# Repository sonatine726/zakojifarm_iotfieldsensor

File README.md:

# 座光寺農園の田んぼの環境センシングIoT機器

# 機能仕様

1. 設置した田んぼの気温、気圧、水位、GPS座標、バッテリー残量といったデータを定期的に計測する
2. 1で計測したデータをLTEでWEBサーバにアップロードする
3. 間欠動作でバッテリー交換無しで１シーズンの長期間駆動を実現する
4. 2のデータはWEBブラウザやスマートフォンアプリで、時系列順の参照や統計処理を可能にする
5. 4のデータに対してメールやMQTTによるアラート通知を可能にする
6. 自動水門開閉機能といった将来的な機能拡張が可能な機構や設計にする

# 成果物の形式と保管場所
## ハードウェア
### 機構
CADデータは Fusion360で作成。保管はFusion Team のクラウドストレージを使用する。
それ以外のデータは本リポジトリに保管。

### 基板
基板データはKiCadで作成。保管は本リポジトリ。

Pcbディレクトリ： 各基板のKiCadデータ

Fritzingディレクトリ： 試作用のFritzingデータ

## ソフトウェア
### クライアント(IoT機器)
本リポジトリに保管。

### サーバ
WEBサービスごとに専用のリポジトリを作って保管

### スマートフォンアプリ
アプリケーションごとに専用のリポジトリを作って保管

# 各成果物のイメージ
## 基板

## 機構
### フラグシップモデル

### エントリーモデル

## 作業風景

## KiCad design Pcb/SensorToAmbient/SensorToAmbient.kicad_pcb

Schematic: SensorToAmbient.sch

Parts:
3SB1: SN74HC125N; DIP-14_W3mm
D1, D2, D3: D_Schottky; D_SOD-323_HandSoldering
DCDC1: PowerBoost500 Basic; DCDC_PowerBoost500
J1: D38 In; Grove_2mm_4pin_angle2
J2: D20 In; Grove_2mm_4pin_angle2
J3: A6 In; Grove_2mm_4pin_angle2
J4: A4 In; Grove_2mm_4pin_angle2
J5: I2C Out; JST_XH_S04B-XH-A_04x2.50mm_Angled
J6: I2C In; Grove_2mm_4pin_angle2
J7: PWR In; JST_PH_S2B-PH-K_02x2.00mm_Angled
J8: MS5540C 1; JST_XH_S06B-XH-A_06x2.50mm_Angled
J9: MS5540C 2; JST_XH_S06B-XH-A_06x2.50mm_Angled
R1, R2, R3, R4, R5: 100K; R_0805_HandSoldering
RTC1: RTC-8564NB; RTC-8564NB_Akiduki
SW1: PWR SW; JST_XH_S02B-XH-A_02x2.50mm_Angled
SW2: Func SW; JST_XH_S02B-XH-A_02x2.50mm_Angled

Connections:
/PWR3.3V_DCDC: D3.2 (A), J4.2
/PWR3.3V_Sensors: J6.2, J8.1, J9.1
/PWR3.3V_Switch: J1.2, SW2.1
/PWR5V: DCDC1.6 (Vout), J5.2
/PWR_BAT: 3SB1.2 (1A), 3SB1.14 (VCC), D1.2 (A), DCDC1.1 (Bat), J7.1, R1.1, R5.2, RTC1.8 (VDD)
GND: 3SB1.7 (GND), DCDC1.2 (GND), DCDC1.5 (GND), J1.1, J2.1, J3.1, J4.1, J5.1, J6.1, J7.2, J8.2, J9.2, R2.2, R3.2, R4.2, RTC1.4 (VSS)
unnamed: 3SB1.1 (1OE), R5.1, RTC1.3 (INT)
unnamed: 3SB1.3 (1Y), D2.2 (A)
unnamed: 3SB1.9 (3A), J9.5
unnamed: 3SB1.10 (3OE), J4.4
unnamed: 3SB1.8 (3Y), 3SB1.11 (4Y), J3.4
unnamed: 3SB1.12 (4A), J8.5
unnamed: 3SB1.13 (4OE), J1.3
unnamed: D1.1 (K), SW1.2
unnamed: D2.1 (K), D3.1 (K), DCDC1.3 (EN), R3.1, SW1.1
unnamed: J1.4, R4.1, SW2.2
unnamed: J2.3, J8.6, J9.6
unnamed: J2.4, J8.3, J9.3, RTC1.2 (CLKOUT)
unnamed: J3.3, J8.4, J9.4
unnamed: J4.3, R1.2, R2.1
unnamed: J5.3, J6.3, RTC1.5 (SDA)
unnamed: J5.4, J6.4, RTC1.6 (SCL)

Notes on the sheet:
I2C SCL
I2C SDA
PWR3.3V
From WioLTE I2C
To LED by I2C
From WioLTE A4
From WioLTE D38
From WioLTE D20
From WioLTE A6
PWR5V
GND
ADC
To Ms5540c 2
To Ms5540c 1
Ms5540C 2 OE
Ms5540c MISO
Ms5540c MOSI
Ms5540c SCK
Ms5540c MCLK(PWM)
Switch DIN
Ms5540C 1 OE
MCLK
DOUT
DIN
SCK
VDD

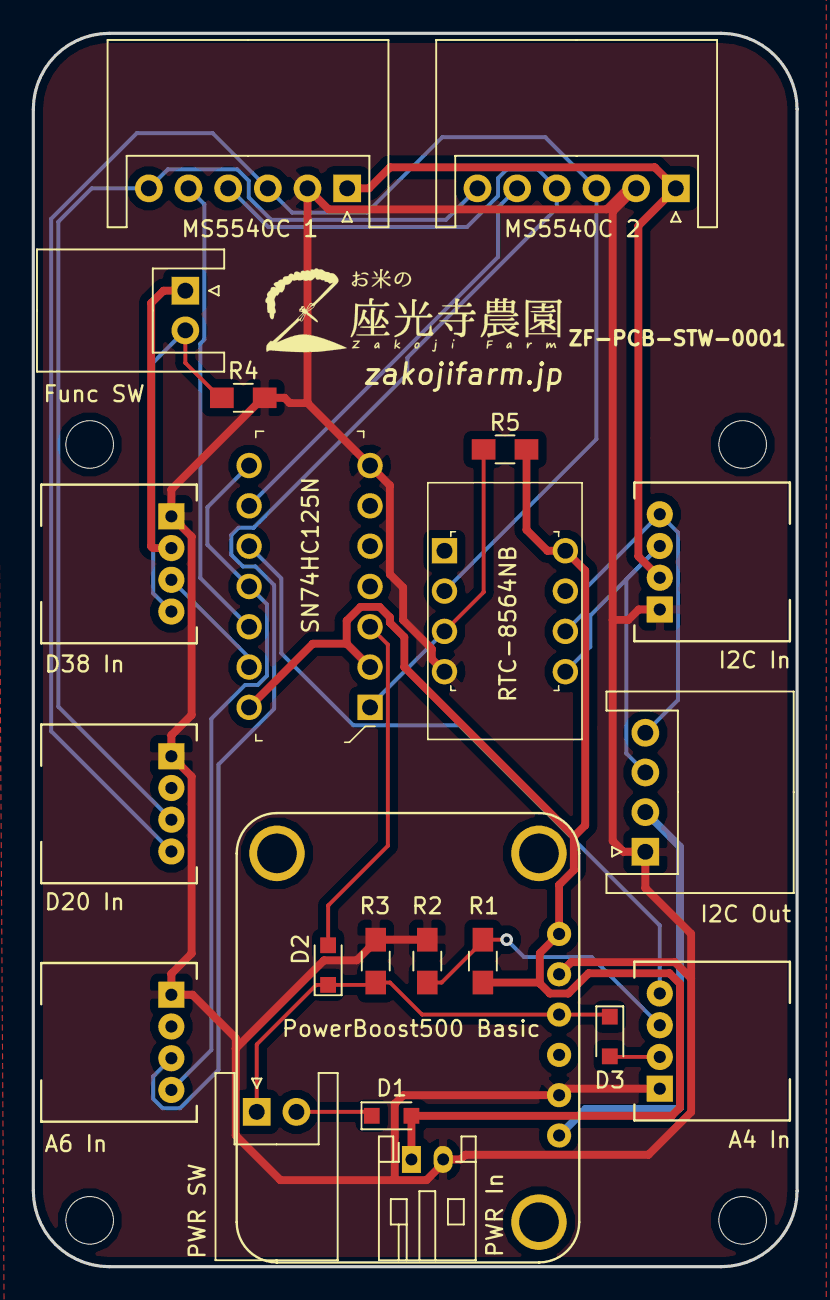
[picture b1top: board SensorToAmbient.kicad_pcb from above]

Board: 2 copper layers, 48.1 x 77.7 mm, 26 parts (0 on the bottom side), 22 nets.

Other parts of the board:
REF1, REF2, REF3, REF4: MountingHole_3mm_rev

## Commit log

2018-08-09 Add initial ino file with function to read temperature and humidity and send these to serial and ambient
2018-08-09 First complete with compile success
2018-08-10 Fix some bugs and pass tests
2018-08-22 Commit intermediate (First compile successed)
2018-08-23 Commit intermediate (Source with debug codes)
2018-08-23 Complete standby mode loop
2018-08-23 Add 1st fzz file
2018-08-23 Fix a little
2018-08-24 First success of compile
2018-08-24 Add .gitignore for visual studio project
2018-08-25 First success to get temperature
2018-08-25 Complete function with deleting debug codes
2018-08-26 Add compile switch C_SW_LTE
2018-08-26 Add compile switch C_SW_AMBIENT
2018-08-26 Add compile switch C_SW_DHT11
2018-08-26 Add compile switch C_SW_DS18B20
2018-08-26 Add compile switch C_SW_GPS
2018-08-26 Commit intermediate ( First success of compile )
2018-08-26 First success to get battery boltage
2018-08-26 Refactor and complete
2018-08-26 Fix a bug that serial print doesn't work in the case only C_SW_BATTERY_V is enabled
2018-08-26 Enable all compile switches
2018-08-31 Set external RTC to make clock to Ms5540c
2018-09-01 Refactor codes for external RTC
2018-09-01 Commit intermediate ( First complete to implement with software SPI class )
2018-09-01 First completion of compile
2018-09-02 Commit intermediate ( Debugging spi to ms5540c )
2018-09-02 Make Ms5540CSPI class for SPI communication to MS5540C with specific pins
2018-09-02 Implement function to make ADC clock for MS5540C by pwm that can be enabled by compile switch
2018-09-04 First success to get pressure and temperature
2018-09-04 Refactor codes for ms5540c with debug codes
2018-09-04 Enable all functions with debug codes
2018-09-15 Commit intermediate ( Adding new parts )
2018-09-16 Add new ambient channnel
2018-09-17 Update substrate design of fritzing
2018-09-21 Add LED and second batteries
2018-09-21 Add initial files of KiCAD
2018-09-21 Move files of Fritzing to folder 'Fritzing'
2018-09-21 Commit intermediate (Making schematics)
2018-09-22 Complete to wire
2018-09-22 Assign foorprints to symbols
2018-09-22 Commit intermediate (Making pcb design)
2018-09-23 Making boardedge and spacer holes
2018-09-23 Complete of footprint layout before first wiring work
2018-09-24 Commit intermediate (before revice part layout for wiring)
2018-09-24 Commit intermediate (Revice schematic for pcb wiring)
2018-09-24 Commit intermediate (Remaining wire is only one GND)
2018-09-24 First comple of wiring
2018-09-24 Fix DRC errors
2018-09-24 Make ground plane
2018-09-24 Add silks
2018-09-24 Add zakojifarm logo on pcb
2018-09-26 Add a 3d model of grove connector
2018-09-26 Improve 3d model of grove connector
2018-09-27 Add a 3D model of RTC for pcb footprint
2018-09-27 Add a 3D model of DCDC for pcb footprint
2018-09-27 Fix commit leak files
2018-09-28 Commit intermediate (Delete Wil LTE outline from pcb)
2018-09-28 Add step files for export pcb step for 3DCAD
2018-09-28 Add pcb 3D model file for fusion360
2018-10-05 Update SensorToAmbient pcb and add wiolte board pcb
2018-10-05 Add housing 3d model
2018-10-05 Get two Ms5540c sensor values and calcurate water level
2018-10-05 Commit intermediate (Implement external RTC alarm for wake up)
2018-10-06 Commit intermediate (Add items for power controll)
2018-10-06 Commit intermediate (Making double-side board)
2018-10-07 Complete making new double-side board
2018-10-08 First success to get values from two Ms5540c
2018-10-08 Add console log displaying water level
2018-10-09 Commit intermediate (Debugging non-stable i2c)
2018-10-09 First complete of external rtc handling (But use workaround for I2C)
2018-10-11 Commit intermediate (Complete of fixing schmatic)
2018-10-11 Commit intermediate (Changing footprints of resistor and diode to SMD)
2018-10-11 Commit intermediate ( First complete of updating pcb )
2018-10-11 Complete fixing pcb board
2018-10-12 Complete running with only battery
2018-10-12 Correct resistor const on pcb
2018-10-13 Update silks on pcb for order
2018-10-14 First succeed at compiling abount managing led codes
2018-10-15 Fix bugs finded in basic tests to manage led function
2018-10-15 Remove workaround for I2c initialization
2018-10-16 Move position of whole pcb
2018-10-16 Adjust pcb design for order
    - Change a resistor for A4 power to diode
    - Fit connectors on the inside of pcb edge
    - Align wires
2018-10-16 Connect all GND pins of grove connectors to battery GND
2019-04-03 Comment on ids
